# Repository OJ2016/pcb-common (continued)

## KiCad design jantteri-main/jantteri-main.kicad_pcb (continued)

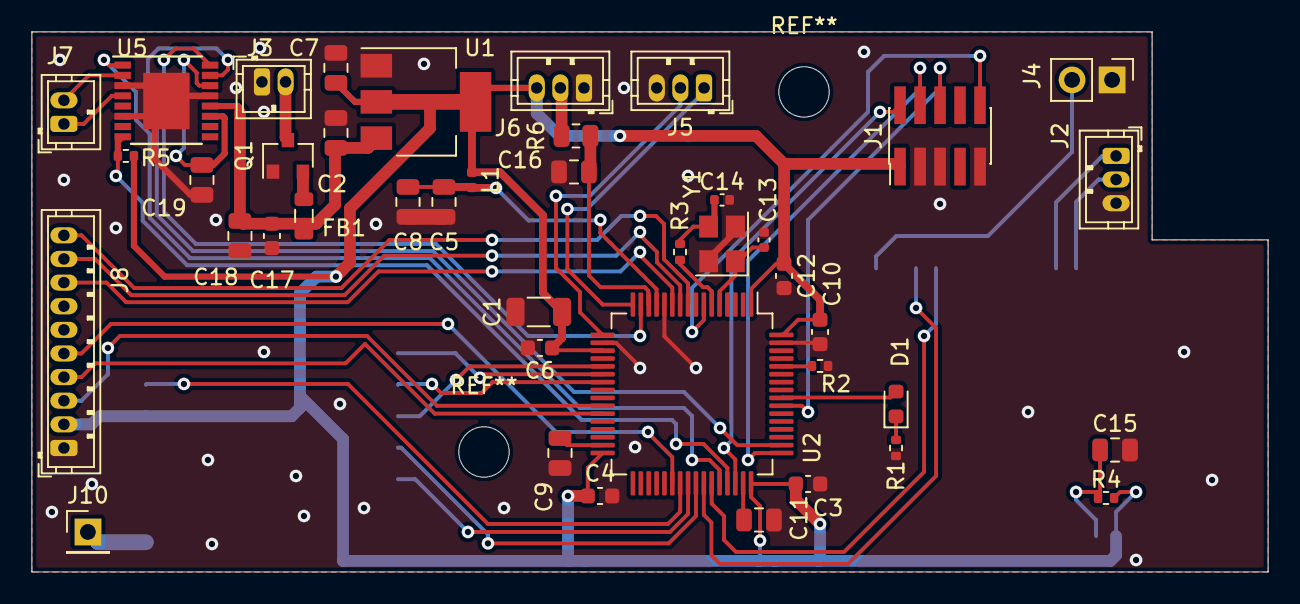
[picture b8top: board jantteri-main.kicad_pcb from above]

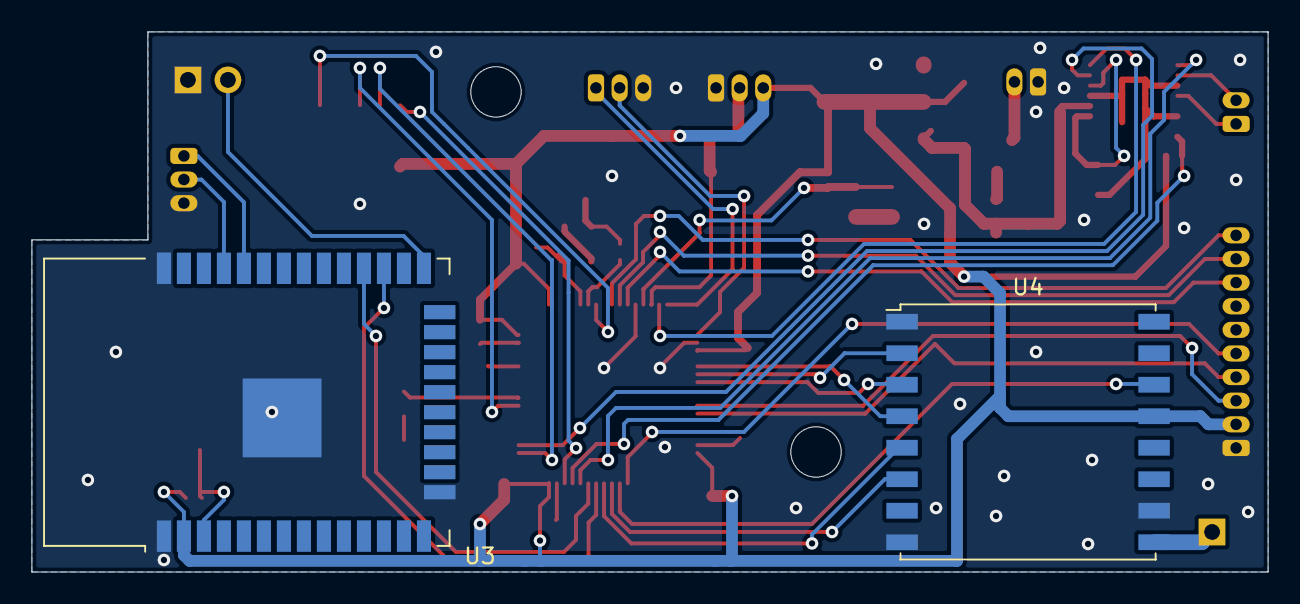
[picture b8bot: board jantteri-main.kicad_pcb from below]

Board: 2 copper layers, 78.5 x 34.3 mm, 44 parts (2 on the bottom side), 48 nets.

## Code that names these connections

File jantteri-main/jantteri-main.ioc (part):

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Mcu.Name=STM32F405RGTx
Mcu.Package=LQFP64
Mcu.UserName=STM32F405RGTx
PA0-WKUP.Signal=ADCx_IN0
PA1.GPIOParameters=GPIO_Label
PA1.GPIO_Label=MOTOR_A
PA1.Signal=S_TIM2_CH2
PA10.GPIOParameters=GPIO_Label
PA10.GPIO_Label=ESP_AT_XR
PA10.Mode=Asynchronous
PA10.Signal=USART1_RX
PA11.GPIOParameters=GPIO_Label
PA11.GPIO_Label=DRV_SLEEP
PA11.Signal=GPIO_Output
PA12.GPIOParameters=GPIO_Label
PA12.GPIO_Label=DRV_FAULT
PA12.Signal=GPIO_Input
PA13.Mode=Trace_Asynchronous_SW
PA13.Signal=SYS_JTMS-SWDIO
PA14.Mode=Trace_Asynchronous_SW
PA14.Signal=SYS_JTCK-SWCLK
PA15.GPIOParameters=GPIO_Label
PA15.GPIO_Label=MOTOR_B
PA15.Signal=S_TIM2_CH1_ETR
PA2.GPIOParameters=GPIO_Label
PA2.GPIO_Label=DBG_TX
PA2.Mode=Asynchronous
PA2.Signal=USART2_TX
PA3.GPIOParameters=GPIO_Label
PA3.GPIO_Label=DBG_RX
PA3.Mode=Asynchronous
PA3.Signal=USART2_RX
PA5.Mode=Full_Duplex_Master
PA5.Signal=SPI1_SCK
PA6.Mode=Full_Duplex_Master
PA6.Signal=SPI1_MISO
PA7.Mode=Full_Duplex_Master
PA7.Signal=SPI1_MOSI
PA8.GPIOParameters=GPIO_Label
PA8.GPIO_Label=RFM_NSS
PA8.Signal=GPIO_Output
PA9.GPIOParameters=GPIO_Label
PA9.GPIO_Label=ESP_AT_TX
PA9.Mode=Asynchronous
PA9.Signal=USART1_TX
PB0.GPIOParameters=GPIO_Label
PB0.GPIO_Label=LED_R
PB0.Signal=S_TIM3_CH3
PB1.GPIOParameters=GPIO_Label
PB1.GPIO_Label=LED_G
PB1.Signal=S_TIM3_CH4
PB3.Mode=Trace_Asynchronous_SW
PB3.Signal=SYS_JTDO-SWO
PB4.GPIOParameters=GPIO_Label
PB4.GPIO_Label=STATUS_LED
PB4.Signal=GPIO_Output
PC1.GPIOParameters=GPIO_Label
PC1.GPIO_Label=OUT1
PC1.Signal=GPIO_Input
PC2.GPIOParameters=GPIO_Label
PC2.GPIO_Label=OUT2
PC2.Signal=GPIO_Input
PC3.GPIOParameters=GPIO_Label
PC3.GPIO_Label=OUT3
PC3.Signal=GPIO_Input
PC7.GPIOParameters=GPIO_Label
PC7.GPIO_Label=LED_B
PC7.Signal=S_TIM3_CH2
PC8.GPIOParameters=GPIO_Label
PC8.GPIO_Label=RFM_DIO0
PC8.Signal=GPIO_Input
PC9.GPIOParameters=GPIO_Label
PC9.GPIO_Label=RFM_RST
PC9.Signal=GPIO_Output
PH0-OSC_IN.Mode=HSE-External-Oscillator
PH0-OSC_IN.Signal=RCC_OSC_IN
PH1-OSC_OUT.Mode=HSE-External-Oscillator
PH1-OSC_OUT.Signal=RCC_OSC_OUT
RCC.HSE_VALUE=25000000
RCC.SYSCLKFreq_VALUE=16000000
board=custom

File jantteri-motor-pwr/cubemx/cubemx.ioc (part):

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Mcu.Name=STM32L151C(6-8-B)TxA
Mcu.Package=LQFP48
Mcu.UserName=STM32L151C8TxA
PA0-WKUP1.Mode=IN0
PA0-WKUP1.Signal=ADC_IN0
PA1.Mode=IN1
PA1.Signal=ADC_IN1
PA10.Mode=Asynchronous
PA10.Signal=USART1_RX
PA11.Mode=Device
PA11.Signal=USB_DM
PA12.Mode=Device
PA12.Signal=USB_DP
PA13.Mode=Trace_Asynchronous_SW
PA13.Signal=SYS_JTMS-SWDIO
PA14.Mode=Trace_Asynchronous_SW
PA14.Signal=SYS_JTCK-SWCLK
PA2.Mode=Asynchronous
PA2.Signal=USART2_TX
PA3.Mode=Asynchronous
PA3.Signal=USART2_RX
PA5.Mode=TX_Only_Simplex_Unidirect_Master
PA5.Signal=SPI1_SCK
PA6.Mode=IN6
PA6.Signal=ADC_IN6
PA7.Mode=TX_Only_Simplex_Unidirect_Master
PA7.Signal=SPI1_MOSI
PA9.Mode=Asynchronous
PA9.Signal=USART1_TX
PB10.Mode=Asynchronous
PB10.Signal=USART3_TX
PB11.Mode=Asynchronous
PB11.Signal=USART3_RX
PB12.Signal=GPIO_Input
PB13.Signal=GPIO_Output
PB14.Signal=GPIO_Output
PB15.Signal=GPIO_Output
PB3.Mode=Trace_Asynchronous_SW
PB3.Signal=SYS_JTDO-TRACESWO
PB6.Mode=I2C
PB6.Signal=I2C1_SCL
PB7.Mode=I2C
PB7.Signal=I2C1_SDA
PB8.Signal=GPIO_Output
PB9.Signal=GPIO_Output
PH0-OSC_IN.Mode=HSE-External-Oscillator
PH0-OSC_IN.Signal=RCC_OSC_IN
PH1-OSC_OUT.Mode=HSE-External-Oscillator
PH1-OSC_OUT.Signal=RCC_OSC_OUT
RCC.HSE_VALUE=16000000
RCC.SYSCLKFreq_VALUE=16000000
RCC.SYSCLKSource=RCC_SYSCLKSOURCE_HSI
board=custom

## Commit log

2021-08-02 add jlc bom script
2021-08-02 add kicad libs
2021-08-10 Add hit detector
2021-08-11 jantteri-motor-pwr and jantteri-lora initial
2021-08-13 jantteri-lora work
2021-08-14 Lora PCB desging
2021-08-15 remove hit-detector i2c pullup resistors
2021-08-16 Lora-module v1
2021-08-17 hit-detector update
2021-08-18 jantteri-pwr-motor
2021-08-19 motor-pwrv2
2021-08-23 revised motor-pwr
2022-05-13 random changes
2022-06-19 Tuubijantteri design Ordered
2022-07-05 fixes
2024-03-29 Add tuubijantteri
2024-04-02 Update jantteri-right to new layout
2024-04-05 update jantteri_right
2024-04-05 add forgotten testrack project
2024-04-05 tuubijantteri order changes
2024-09-05 Update projects
